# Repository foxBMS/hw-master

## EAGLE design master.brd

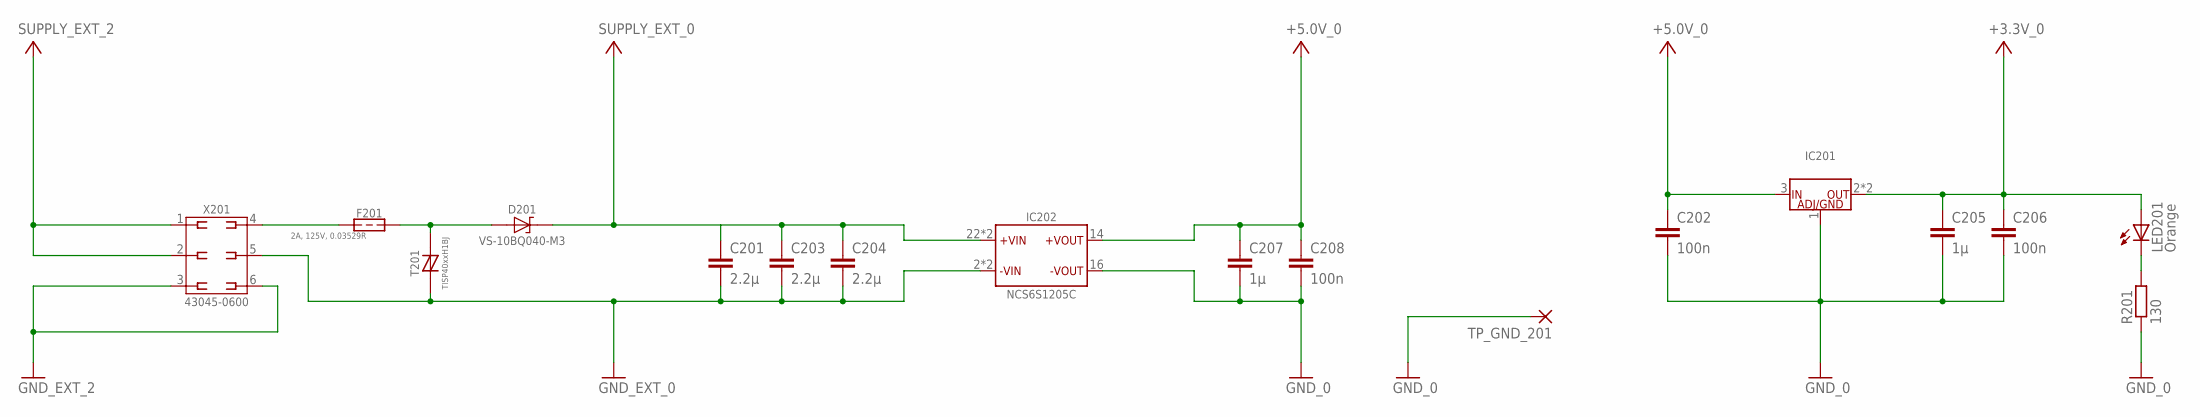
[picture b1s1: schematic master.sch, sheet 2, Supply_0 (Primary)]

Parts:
C201, C203, C204: 2.2µ; C0805
C202, C206, C208: 100n; C0603
C205, C207: 1µ; C0603
D201: VS-10BQ040-M3; D_SMD_SMB_(DO-214AA)_R_VISHAY_REV01
F201: 0,500A_LITTELFUSE_4482A; 448_SERIES_LITTELFUSE
IC201: LM1085IS-5.0/NOPB; IC_SMD_TO-263-3_(KTT0003B)_R_TI_REV01
IC202: MURATA_NCS6S1205C; IC_TH_32,00MMX20,00MMX10,00MM_(7-PIN)_R_MURATA_REV01
LED201: Orange; CHIP-LED0603
R201: 130; R0603
T201: TISP40XXH1BJ; TVS_THYRISTOR
TP_GND_201: 1,6/0,8
X201: 43045-0600_MOLEX_6PIN; X_TH_MOLEX_43045-0600_R_REV01

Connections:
+3.3V_0: C205.1, C206.1, IC201.2 (OUT), IC201.4 (OUT), LED201.A; also elsewhere on the board
+5.0V_0: C202.1, C207.1, C208.1, IC201.3 (IN), IC202.14 (+VOUT); also elsewhere on the board
GND_0: C202.2, C205.2, C206.2, C207.2, C208.2, IC201.1 (ADJ/GND), IC202.16 (-VOUT), R201.1, TP_GND_201.1; also elsewhere on the board
GND_EXT_0: C201.2, C203.2, C204.2, IC202.2 (-VIN), IC202.3 (-VIN), T201.C (T), X201.5; also elsewhere on the board
GND_EXT_2: X201.3, X201.6; also elsewhere on the board
unnamed: LED201.C, R201.2
unnamed: D201.A, F201.P$2, T201.A (R)
unnamed: F201.P$1, X201.4
SUPPLY_EXT_0: C201.1, C203.1, C204.1, D201.C, IC202.22 (+VIN), IC202.23 (+VIN); also elsewhere on the board
SUPPLY_EXT_2: X201.1, X201.2; also elsewhere on the board

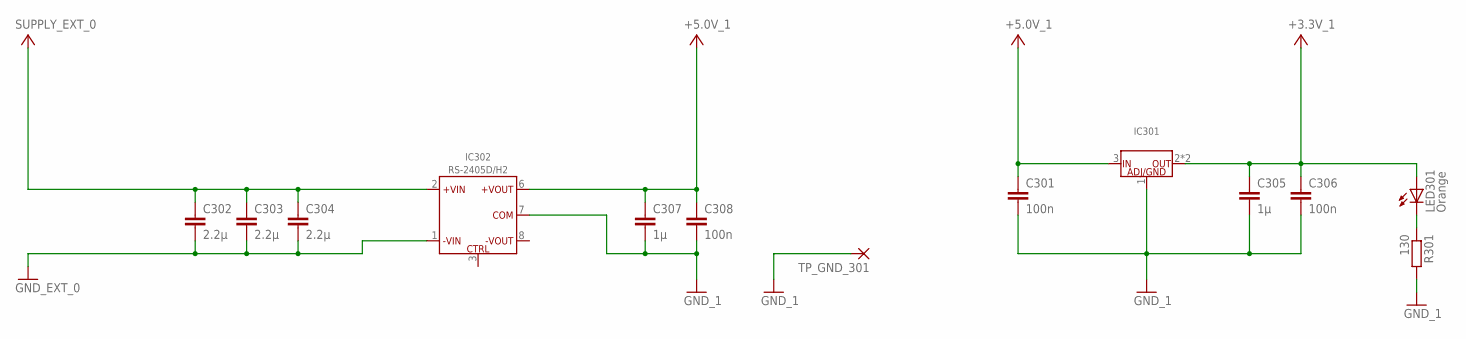
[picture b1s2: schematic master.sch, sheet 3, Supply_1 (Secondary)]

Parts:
C301, C306, C308: 100n; C0603
C302, C303, C304: 2.2µ; C0805
C305, C307: 1µ; C0603
IC301: LM1085IS-5.0/NOPB; IC_SMD_TO-263-3_(KTT0003B)_R_TI_REV01
IC302: RS-2405D/H2; IC_TH_SIP8_R_RECOM_REV01
LED301: Orange; CHIP-LED0603
R301: 130; R0603
TP_GND_301: 1,6/0,8

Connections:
+3.3V_1: C305.1, C306.1, IC301.2 (OUT), IC301.4 (OUT), LED301.A; also elsewhere on the board
+5.0V_1: C301.1, C307.1, C308.1, IC301.3 (IN), IC302.6 (+VOUT); also elsewhere on the board
GND_1: C301.2, C305.2, C306.2, C307.2, C308.2, IC301.1 (ADJ/GND), IC302.7 (COM), R301.2, TP_GND_301.1; also elsewhere on the board
GND_EXT_0: C302.2, C303.2, C304.2, IC302.1 (-VIN); also elsewhere on the board
unnamed: LED301.C, R301.1
SUPPLY_EXT_0: C302.1, C303.1, C304.1, IC302.2 (+VIN); also elsewhere on the board

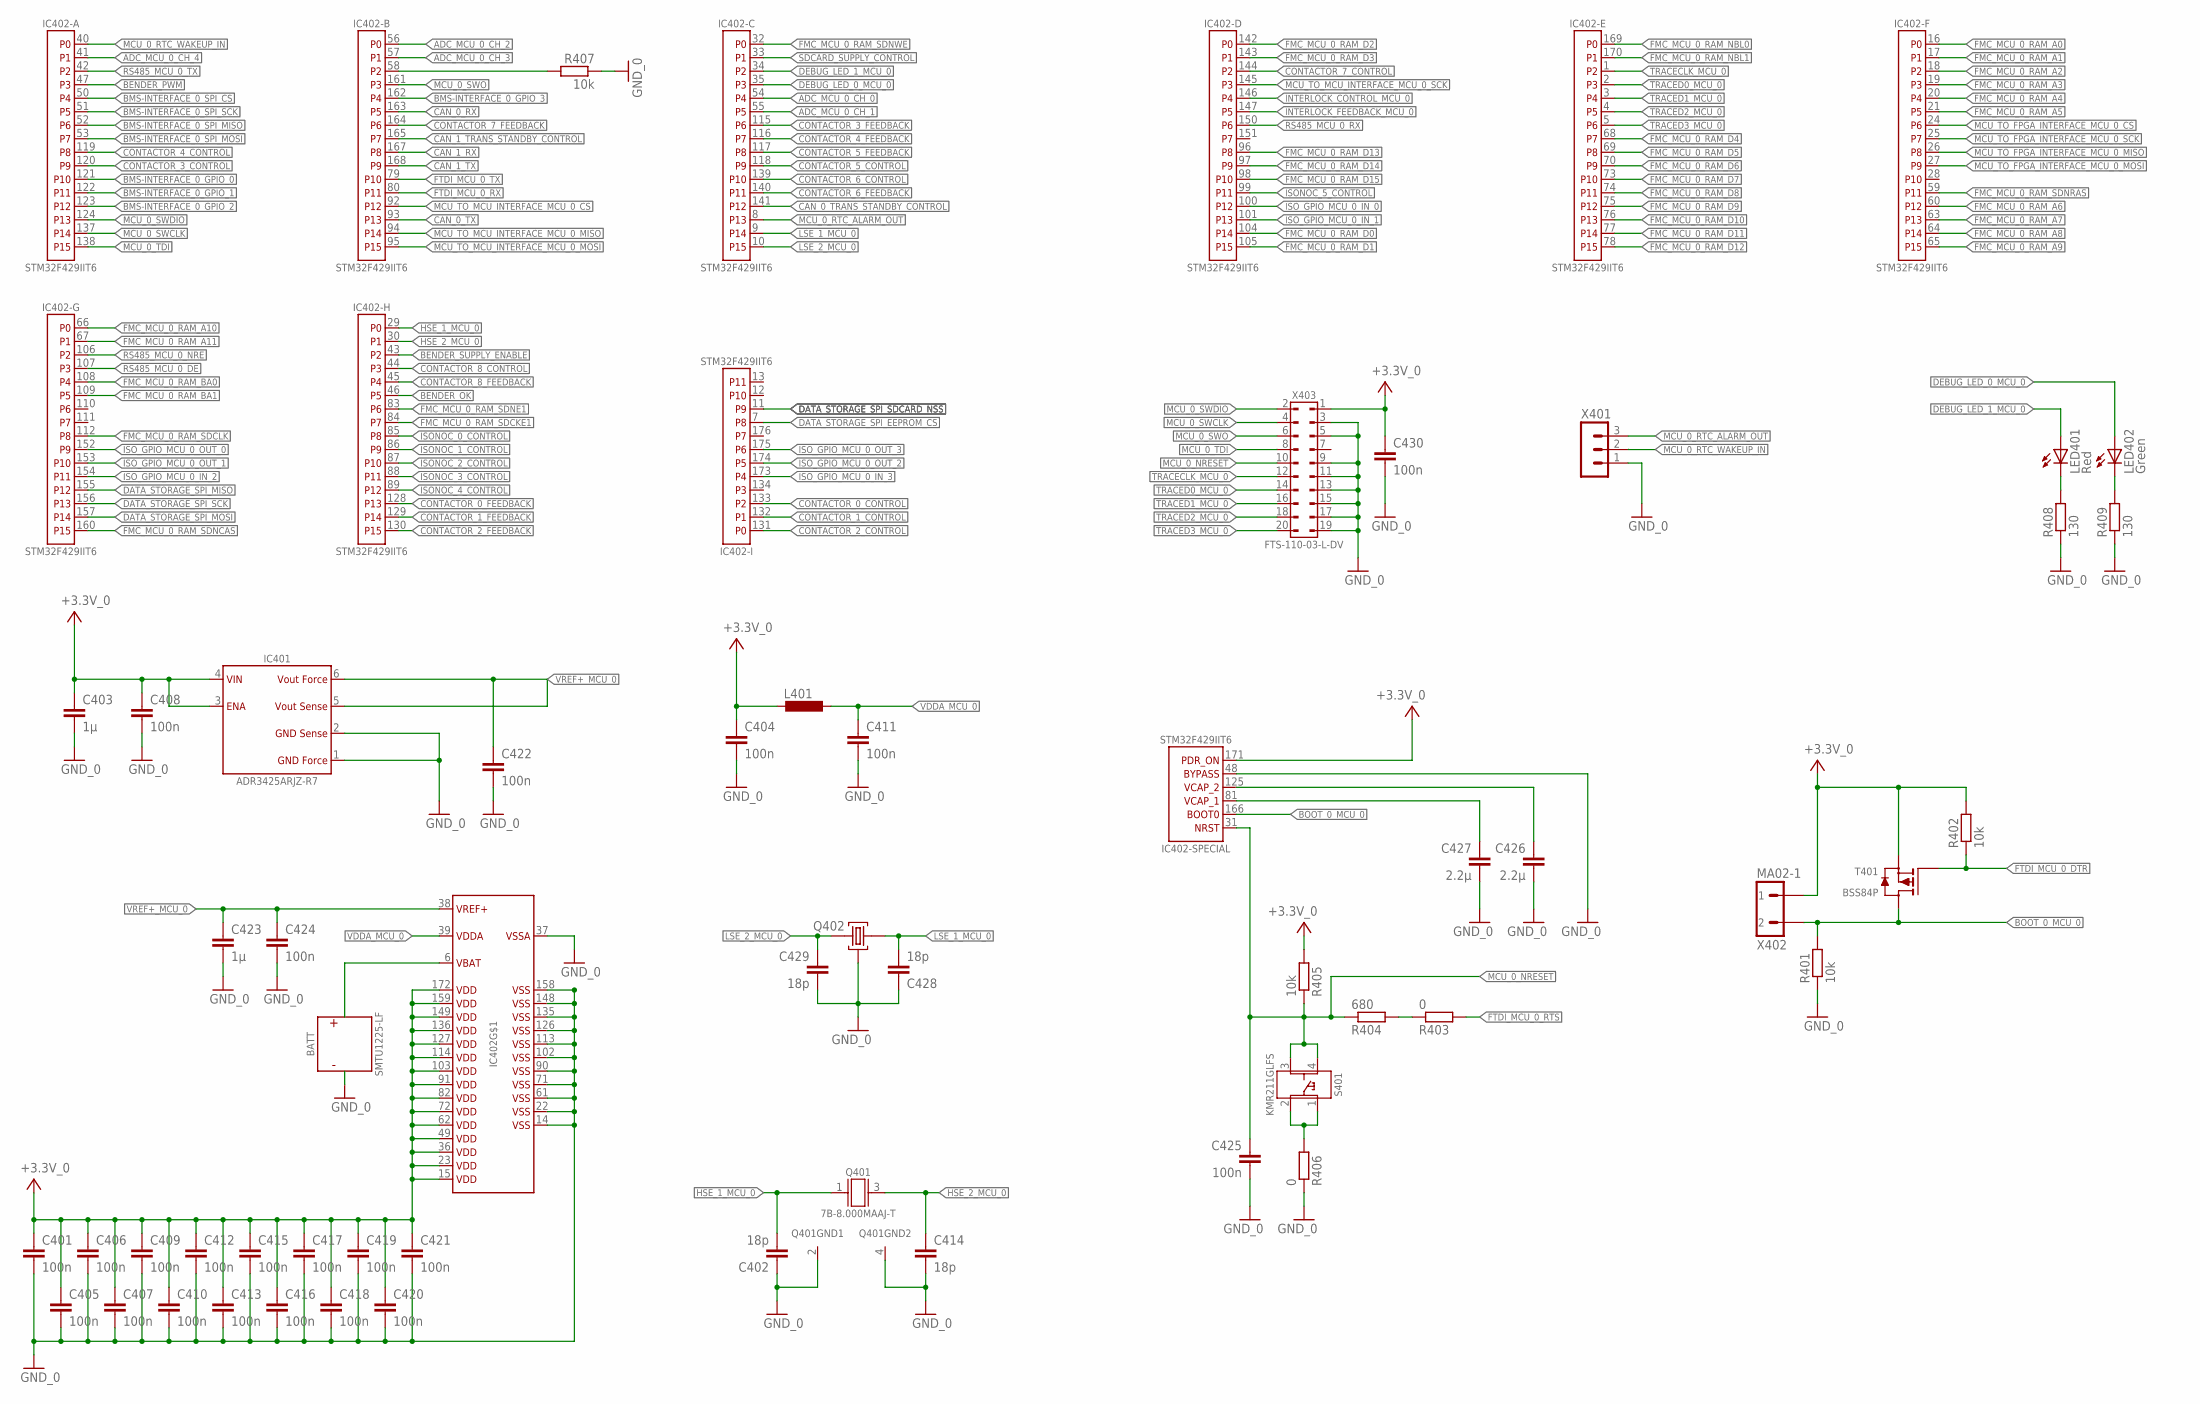
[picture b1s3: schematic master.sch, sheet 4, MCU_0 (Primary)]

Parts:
BATT: SMTU1225-LF; X_SMD_(23,70MM_X_12,70MM_X_5,00MM)_R_RENATA_REV01
C401, C404, C405, C406, C407, C408, C409, C410, C411, C412, C413, C415, C416, C417, C418, C419, C420, C421, C422, C424, C425, C430: 100n; C0603
C402, C414, C428, C429: 18p; C0603
C403, C423: 1µ; C0603
C426, C427: 2.2µ; C0603
IC401: ADR3425ARJZ; IC_SMD_SOT23-6_(MO-178-AB)_R_AD_REV01
IC402: STM32F429IIT6; IC_SMD_LQFP176_R_ST_REV01
L401: L0805; 0805
LED401: Red; CHIP-LED0603
LED402: Green; CHIP-LED0603
Q401: 7B-8.000MAAJ-T; G_SMD_5,00MM_X_3,20MM_0,90MM_(7B)_TXC_REV01
Q402: MS3V; MS3V-T1R
R401, R402, R405, R407: 10k; R0603
R403, R406: 0; R0603
R404: 680; R0603
R408, R409: 130; R0603
S401: KMR211GLFS; S_SMD_4,60MMX2,80MMX1,90MM_R_CK-COMPONENTS_REV01
T401: BSS84P; V_SMD_SOT23_(TO-236AB)_R_INFINEON_REV01
X401: MA03-1
X402: MA02-1
X403: SAMTEC_FTS_20POL_HEADER_VERTIKAL_REV01; X_SMD_FTS_110-03_(20POL)_R_SAMTEC_REV01

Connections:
+3.3V_0: C401.1, C403.1, C404.1, C405.1, C406.1, C407.1, C408.1, C409.1, C410.1, C412.1, C413.1, C415.1, C416.1, C417.1, C418.1, C419.1, C420.1, C421.1, C430.1, IC401.3 (ENABLE), IC401.4 (VIN), IC402.15 (VDD1), IC402.23 (VDD2), IC402.36 (VDD3), IC402.49 (VDD4), IC402.62 (VDD5), IC402.72 (VDD6), IC402.82 (VDD7), IC402.91 (VDD8), IC402.103 (VDD9), IC402.114 (VDD10), IC402.127 (VDD11), IC402.136 (VDD12), IC402.149 (VDD13), IC402.159 (VDD14), IC402.171 (PDR_ON), IC402.172 (VDD15), L401.1, R402.2, R405.2, T401.2 (S), X402.1, X403.1; also elsewhere on the board
ADC_MCU_0_CH_0: IC402.54 (P4); also elsewhere on the board
ADC_MCU_0_CH_1: IC402.55 (P5); also elsewhere on the board
ADC_MCU_0_CH_2: IC402.56 (P0); also elsewhere on the board
ADC_MCU_0_CH_3: IC402.57 (P1); also elsewhere on the board
ADC_MCU_0_CH_4: IC402.41 (P1); also elsewhere on the board
BENDER_OK: IC402.46 (P5); also elsewhere on the board
BENDER_PWM: IC402.47 (P3); also elsewhere on the board
BENDER_SUPPLY_ENABLE: IC402.43 (P2); also elsewhere on the board
BMS-INTERFACE_0_GPIO_0: IC402.121 (P10); also elsewhere on the board
BMS-INTERFACE_0_GPIO_1: IC402.122 (P11); also elsewhere on the board
BMS-INTERFACE_0_GPIO_2: IC402.123 (P12); also elsewhere on the board
BMS-INTERFACE_0_GPIO_3: IC402.162 (P4); also elsewhere on the board
BMS-INTERFACE_0_SPI_CS: IC402.50 (P4); also elsewhere on the board
BMS-INTERFACE_0_SPI_MISO: IC402.52 (P6); also elsewhere on the board
BMS-INTERFACE_0_SPI_MOSI: IC402.53 (P7); also elsewhere on the board
BMS-INTERFACE_0_SPI_SCK: IC402.51 (P5); also elsewhere on the board
BOOT_0_MCU_0: IC402.166 (BOOT0), R401.2, T401.3 (D), X402.2
CAN_0_RX: IC402.163 (P5); also elsewhere on the board
CAN_0_TRANS_STANDBY_CONTROL: IC402.141 (P12); also elsewhere on the board
CAN_0_TX: IC402.93 (P13); also elsewhere on the board
CAN_1_RX: IC402.167 (P8); also elsewhere on the board
CAN_1_TRANS_STANDBY_CONTROL: IC402.165 (P7); also elsewhere on the board
CAN_1_TX: IC402.168 (P9); also elsewhere on the board
CONTACTOR_0_CONTROL: IC402.133 (P2); also elsewhere on the board
CONTACTOR_0_FEEDBACK: IC402.128 (P13); also elsewhere on the board
CONTACTOR_1_CONTROL: IC402.132 (P1); also elsewhere on the board
CONTACTOR_1_FEEDBACK: IC402.129 (P14); also elsewhere on the board
CONTACTOR_2_CONTROL: IC402.131 (P0); also elsewhere on the board
CONTACTOR_2_FEEDBACK: IC402.130 (P15); also elsewhere on the board
CONTACTOR_3_CONTROL: IC402.120 (P9); also elsewhere on the board
CONTACTOR_3_FEEDBACK: IC402.115 (P6); also elsewhere on the board
CONTACTOR_4_CONTROL: IC402.119 (P8); also elsewhere on the board
CONTACTOR_4_FEEDBACK: IC402.116 (P7); also elsewhere on the board
CONTACTOR_5_CONTROL: IC402.118 (P9); also elsewhere on the board
CONTACTOR_5_FEEDBACK: IC402.117 (P8); also elsewhere on the board
CONTACTOR_6_CONTROL: IC402.139 (P10); also elsewhere on the board
CONTACTOR_6_FEEDBACK: IC402.140 (P11); also elsewhere on the board
CONTACTOR_7_CONTROL: IC402.144 (P2); also elsewhere on the board
CONTACTOR_7_FEEDBACK: IC402.164 (P6); also elsewhere on the board
CONTACTOR_8_CONTROL: IC402.44 (P3); also elsewhere on the board
CONTACTOR_8_FEEDBACK: IC402.45 (P4); also elsewhere on the board
DATA_STORAGE_SPI_EEPROM_CS: IC402.7 (P8); also elsewhere on the board
DATA_STORAGE_SPI_MISO: IC402.155 (P12); also elsewhere on the board
DATA_STORAGE_SPI_MOSI: IC402.157 (P14); also elsewhere on the board
DATA_STORAGE_SPI_SCK: IC402.156 (P13); also elsewhere on the board
DATA_STORAGE_SPI_SDCARD_NSS: IC402.11 (P9); also elsewhere on the board
DEBUG_LED_0_MCU_0: IC402.35 (P3), LED402.A
DEBUG_LED_1_MCU_0: IC402.34 (P2), LED401.A
FMC_MCU_0_RAM_A0: IC402.16 (P0); also elsewhere on the board
FMC_MCU_0_RAM_A1: IC402.17 (P1); also elsewhere on the board
FMC_MCU_0_RAM_A2: IC402.18 (P2); also elsewhere on the board
FMC_MCU_0_RAM_A3: IC402.19 (P3); also elsewhere on the board
FMC_MCU_0_RAM_A4: IC402.20 (P4); also elsewhere on the board
FMC_MCU_0_RAM_A5: IC402.21 (P5); also elsewhere on the board
FMC_MCU_0_RAM_A6: IC402.60 (P12); also elsewhere on the board
FMC_MCU_0_RAM_A7: IC402.63 (P13); also elsewhere on the board
FMC_MCU_0_RAM_A8: IC402.64 (P14); also elsewhere on the board
FMC_MCU_0_RAM_A9: IC402.65 (P15); also elsewhere on the board
FMC_MCU_0_RAM_A10: IC402.66 (P0); also elsewhere on the board
FMC_MCU_0_RAM_A11: IC402.67 (P1); also elsewhere on the board
FMC_MCU_0_RAM_BA0: IC402.108 (P4); also elsewhere on the board
FMC_MCU_0_RAM_BA1: IC402.109 (P5); also elsewhere on the board
FMC_MCU_0_RAM_D0: IC402.104 (P14); also elsewhere on the board
FMC_MCU_0_RAM_D1: IC402.105 (P15); also elsewhere on the board
FMC_MCU_0_RAM_D2: IC402.142 (P0); also elsewhere on the board
FMC_MCU_0_RAM_D3: IC402.143 (P1); also elsewhere on the board
FMC_MCU_0_RAM_D4: IC402.68 (P7); also elsewhere on the board
FMC_MCU_0_RAM_D5: IC402.69 (P8); also elsewhere on the board
FMC_MCU_0_RAM_D6: IC402.70 (P9); also elsewhere on the board
FMC_MCU_0_RAM_D7: IC402.73 (P10); also elsewhere on the board
FMC_MCU_0_RAM_D8: IC402.74 (P11); also elsewhere on the board
FMC_MCU_0_RAM_D9: IC402.75 (P12); also elsewhere on the board
FMC_MCU_0_RAM_D10: IC402.76 (P13); also elsewhere on the board
FMC_MCU_0_RAM_D11: IC402.77 (P14); also elsewhere on the board
FMC_MCU_0_RAM_D12: IC402.78 (P15); also elsewhere on the board
FMC_MCU_0_RAM_D13: IC402.96 (P8); also elsewhere on the board
FMC_MCU_0_RAM_D14: IC402.97 (P9); also elsewhere on the board
FMC_MCU_0_RAM_D15: IC402.98 (P10); also elsewhere on the board
FMC_MCU_0_RAM_NBL0: IC402.169 (P0); also elsewhere on the board
FMC_MCU_0_RAM_NBL1: IC402.170 (P1); also elsewhere on the board
FMC_MCU_0_RAM_SDCKE1: IC402.84 (P7); also elsewhere on the board
FMC_MCU_0_RAM_SDCLK: IC402.112 (P8); also elsewhere on the board
FMC_MCU_0_RAM_SDNCAS: IC402.160 (P15); also elsewhere on the board
FMC_MCU_0_RAM_SDNE1: IC402.83 (P6); also elsewhere on the board
FMC_MCU_0_RAM_SDNRAS: IC402.59 (P11); also elsewhere on the board
FMC_MCU_0_RAM_SDNWE: IC402.32 (P0); also elsewhere on the board
FTDI_MCU_0_DTR: R402.1, T401.1 (G); also elsewhere on the board
FTDI_MCU_0_RTS: R403.2; also elsewhere on the board
FTDI_MCU_0_RX: IC402.80 (P11); also elsewhere on the board
FTDI_MCU_0_TX: IC402.79 (P10); also elsewhere on the board
GND_0: BATT.-, C401.2, C402.1, C403.2, C404.2, C405.2, C406.2, C407.2, C408.2, C409.2, C410.2, C411.2, C412.2, C413.2, C414.2, C415.2, C416.2, C417.2, C418.2, C419.2, C420.2, C421.2, C422.2, C423.2, C424.2, C425.2, C426.2, C427.2, C428.1, C429.2, C430.2, IC401.1 (GND_FORCE), IC401.2 (GND_SENSE), IC402.14 (VSS1), IC402.22 (VSS2), IC402.37 (VSSA), IC402.48 (BYPASS_REG), IC402.61 (VSS3), IC402.71 (VSS4), IC402.90 (VSS5), IC402.102 (VSS6), IC402.113 (VSS7), IC402.126 (VSS8), IC402.135 (VSS9), IC402.148 (VSS10), IC402.158 (VSS11), Q401.2 (GND), Q401.4 (GND), Q402.P$3 (2), R401.1, R406.1, R407.1, R408.1, R409.1, X401.1, X403.3, X403.5, X403.9, X403.11, X403.13, X403.15, X403.17, X403.19; also elsewhere on the board
HSE_1_MCU_0: C402.2, IC402.29 (P0), Q401.1 (A)
HSE_2_MCU_0: C414.1, IC402.30 (P1), Q401.3 (B)
INTERLOCK_CONTROL_MCU_0: IC402.146 (P4); also elsewhere on the board
INTERLOCK_FEEDBACK_MCU_0: IC402.147 (P5); also elsewhere on the board
ISONOC_0_CONTROL: IC402.85 (P8); also elsewhere on the board
ISONOC_1_CONTROL: IC402.86 (P9); also elsewhere on the board
ISONOC_2_CONTROL: IC402.87 (P10); also elsewhere on the board
ISONOC_3_CONTROL: IC402.88 (P11); also elsewhere on the board
ISONOC_4_CONTROL: IC402.89 (P12); also elsewhere on the board
ISONOC_5_CONTROL: IC402.99 (P11); also elsewhere on the board
ISO_GPIO_MCU_0_IN_0: IC402.100 (P12); also elsewhere on the board
ISO_GPIO_MCU_0_IN_1: IC402.101 (P13); also elsewhere on the board
ISO_GPIO_MCU_0_IN_2: IC402.154 (P11); also elsewhere on the board
ISO_GPIO_MCU_0_IN_3: IC402.173 (P4); also elsewhere on the board
ISO_GPIO_MCU_0_OUT_0: IC402.152 (P9); also elsewhere on the board
ISO_GPIO_MCU_0_OUT_1: IC402.153 (P10); also elsewhere on the board
ISO_GPIO_MCU_0_OUT_2: IC402.174 (P5); also elsewhere on the board
ISO_GPIO_MCU_0_OUT_3: IC402.175 (P6); also elsewhere on the board
LSE_1_MCU_0: C428.2, IC402.9 (P14), Q402.1
LSE_2_MCU_0: C429.1, IC402.10 (P15), Q402.2 (3)
MCU_0_NRESET: C425.1, IC402.31 (NRST), R404.1, R405.1, S401.3, S401.4, X403.10
MCU_0_RTC_ALARM_OUT: IC402.8 (P13), X401.3
MCU_0_RTC_WAKEUP_IN: IC402.40 (P0), X401.2
MCU_0_SWCLK: IC402.137 (P14), X403.4
MCU_0_SWDIO: IC402.124 (P13), X403.2
MCU_0_SWO: IC402.161 (P3), X403.6
MCU_0_TDI: IC402.138 (P15), X403.8
MCU_TO_FPGA_INTERFACE_MCU_0_CS: IC402.24 (P6); also elsewhere on the board
MCU_TO_FPGA_INTERFACE_MCU_0_MISO: IC402.26 (P8); also elsewhere on the board
MCU_TO_FPGA_INTERFACE_MCU_0_MOSI: IC402.27 (P9); also elsewhere on the board
MCU_TO_FPGA_INTERFACE_MCU_0_SCK: IC402.25 (P7); also elsewhere on the board
MCU_TO_MCU_INTERFACE_MCU_0_CS: IC402.92 (P12); also elsewhere on the board
MCU_TO_MCU_INTERFACE_MCU_0_MISO: IC402.94 (P14); also elsewhere on the board
MCU_TO_MCU_INTERFACE_MCU_0_MOSI: IC402.95 (P15); also elsewhere on the board
MCU_TO_MCU_INTERFACE_MCU_0_SCK: IC402.145 (P3); also elsewhere on the board
unnamed: C426.1, IC402.125 (VCAP_2)
unnamed: R406.2, S401.1, S401.2
unnamed: LED401.C, R408.2
unnamed: LED402.C, R409.2
unnamed: C427.1, IC402.81 (VCAP_1)
unnamed: IC402.58 (P2), R407.2
unnamed: R403.1, R404.2
unnamed: BATT.+, IC402.6 (VBAT)
RS485_MCU_0_DE: IC402.107 (P3); also elsewhere on the board
RS485_MCU_0_NRE: IC402.106 (P2); also elsewhere on the board
RS485_MCU_0_RX: IC402.150 (P6); also elsewhere on the board
RS485_MCU_0_TX: IC402.42 (P2); also elsewhere on the board
SDCARD_SUPPLY_CONTROL: IC402.33 (P1); also elsewhere on the board
TRACECLK_MCU_0: IC402.1 (P2), X403.12
TRACED0_MCU_0: IC402.2 (P3), X403.14
TRACED1_MCU_0: IC402.3 (P4), X403.16
TRACED2_MCU_0: IC402.4 (P5), X403.18
TRACED3_MCU_0: IC402.5 (P6), X403.20
VDDA_MCU_0: C411.1, IC402.39 (VDDA), L401.2
VREF+_MCU_0: C422.1, C423.1, C424.1, IC401.5 (VOUT_SENSE), IC401.6 (VOUT_FORCE), IC402.38 (VREF+)

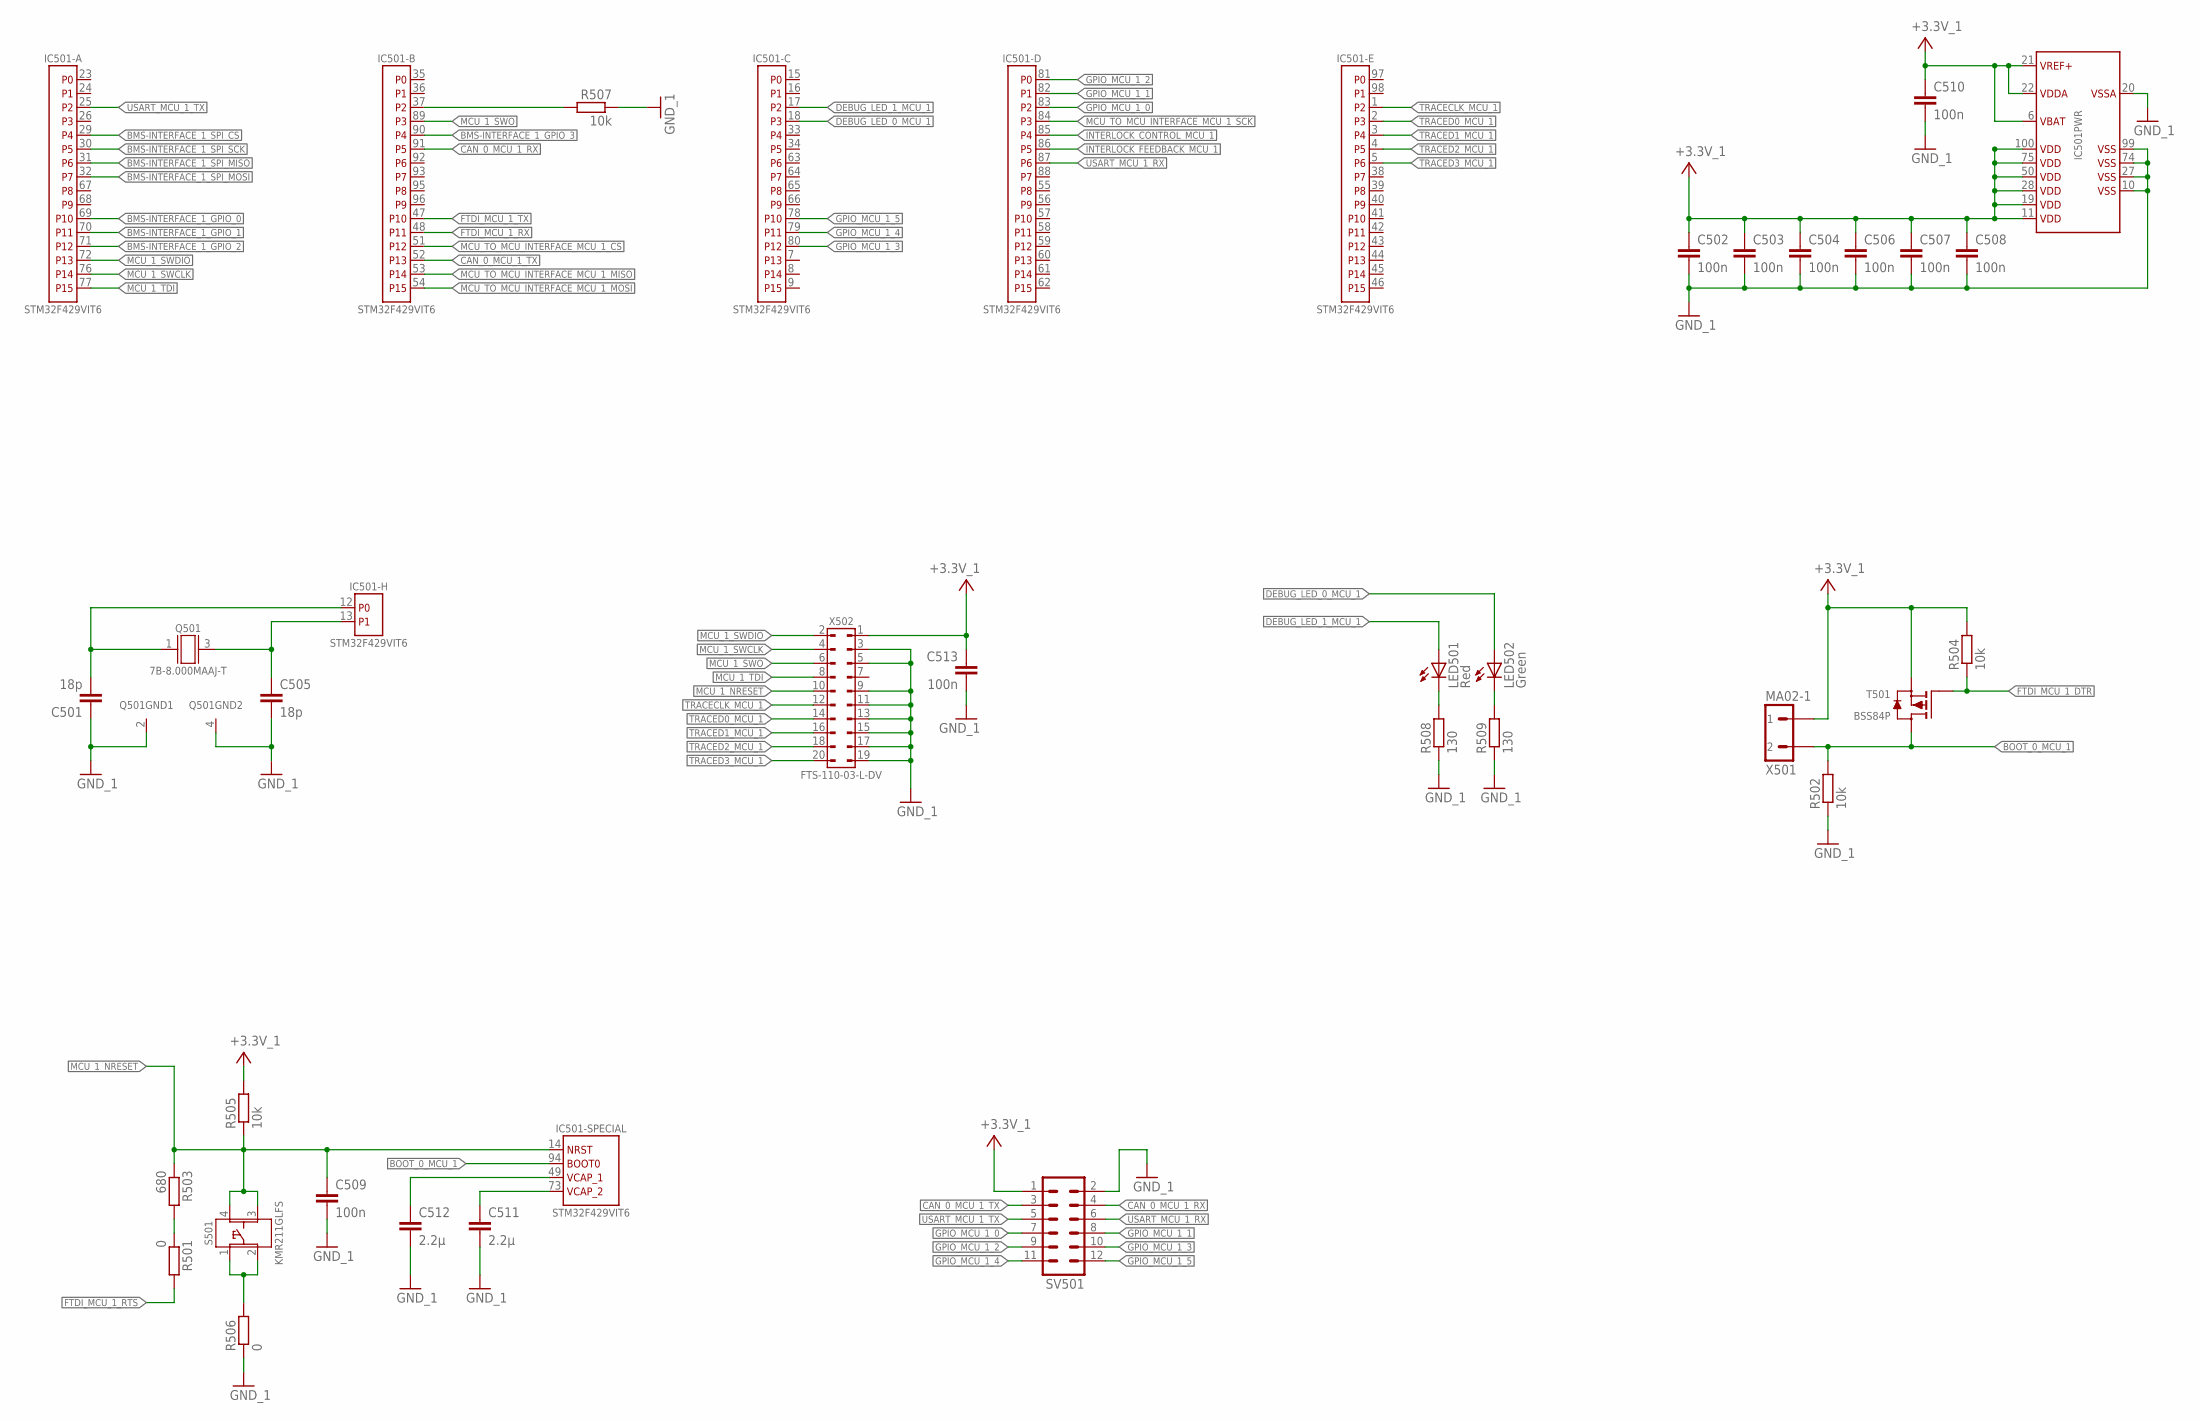
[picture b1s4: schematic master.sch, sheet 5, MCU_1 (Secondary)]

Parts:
C501, C505: 18p; C0603
C502, C503, C504, C506, C507, C508, C509, C510, C513: 100n; C0603
C511, C512: 2.2µ; C0603
IC501: STM32F429VIT6; IC_SMD_LQFP100_R_ST_REV01
LED501: Red; CHIP-LED0603
LED502: Green; CHIP-LED0603
Q501: 7B-8.000MAAJ-T; G_SMD_5,00MM_X_3,20MM_0,90MM_(7B)_TXC_REV01
R501, R506: 0; R0603
R502, R504, R505, R507: 10k; R0603
R503: 680; R0603
R508, R509: 130; R0603
S501: KMR211GLFS; S_SMD_4,60MMX2,80MMX1,90MM_R_CK-COMPONENTS_REV01
SV501: MA06-2
T501: BSS84P; V_SMD_SOT23_(TO-236AB)_R_INFINEON_REV01
X501: MA02-1
X502: SAMTEC_FTS_20POL_HEADER_VERTIKAL_REV01; X_SMD_FTS_110-03_(20POL)_R_SAMTEC_REV01

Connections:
+3.3V_1: C502.1, C503.1, C504.1, C506.1, C507.1, C508.1, C510.1, C513.1, IC501.6 (VBAT), IC501.11 (VDD1), IC501.19 (VDD2), IC501.21 (VREF+), IC501.22 (VDDA), IC501.28 (VDD3), IC501.50 (VDD4), IC501.75 (VDD5), IC501.100 (VDD6), R504.2, R505.2, SV501.1, T501.2 (S), X501.1, X502.1; also elsewhere on the board
BMS-INTERFACE_1_GPIO_0: IC501.69 (P10); also elsewhere on the board
BMS-INTERFACE_1_GPIO_1: IC501.70 (P11); also elsewhere on the board
BMS-INTERFACE_1_GPIO_2: IC501.71 (P12); also elsewhere on the board
BMS-INTERFACE_1_GPIO_3: IC501.90 (P4); also elsewhere on the board
BMS-INTERFACE_1_SPI_CS: IC501.29 (P4); also elsewhere on the board
BMS-INTERFACE_1_SPI_MISO: IC501.31 (P6); also elsewhere on the board
BMS-INTERFACE_1_SPI_MOSI: IC501.32 (P7); also elsewhere on the board
BMS-INTERFACE_1_SPI_SCK: IC501.30 (P5); also elsewhere on the board
BOOT_0_MCU_1: IC501.94 (BOOT0), R502.2, T501.3 (D), X501.2
CAN_0_MCU_1_RX: IC501.91 (P5), SV501.4
CAN_0_MCU_1_TX: IC501.52 (P13), SV501.3
DEBUG_LED_0_MCU_1: IC501.18 (P3), LED502.A
DEBUG_LED_1_MCU_1: IC501.17 (P2), LED501.A
FTDI_MCU_1_DTR: R504.1, T501.1 (G); also elsewhere on the board
FTDI_MCU_1_RTS: R501.2; also elsewhere on the board
FTDI_MCU_1_RX: IC501.48 (P11); also elsewhere on the board
FTDI_MCU_1_TX: IC501.47 (P10); also elsewhere on the board
GND_1: C501.1, C502.2, C503.2, C504.2, C505.2, C506.2, C507.2, C508.2, C509.2, C510.2, C511.2, C512.2, C513.2, IC501.10 (VSS1), IC501.20 (VSSA), IC501.27 (VSS2), IC501.74 (VSS3), IC501.99 (VSS4), Q501.2 (GND), Q501.4 (GND), R502.1, R506.1, R507.1, R508.1, R509.1, SV501.2, X502.3, X502.5, X502.9, X502.11, X502.13, X502.15, X502.17, X502.19; also elsewhere on the board
GPIO_MCU_1_0: IC501.83 (P2), SV501.7
GPIO_MCU_1_1: IC501.82 (P1), SV501.8
GPIO_MCU_1_2: IC501.81 (P0), SV501.9
GPIO_MCU_1_3: IC501.80 (P12), SV501.10
GPIO_MCU_1_4: IC501.79 (P11), SV501.11
GPIO_MCU_1_5: IC501.78 (P10), SV501.12
INTERLOCK_CONTROL_MCU_1: IC501.85 (P4); also elsewhere on the board
INTERLOCK_FEEDBACK_MCU_1: IC501.86 (P5); also elsewhere on the board
MCU_1_NRESET: C509.1, IC501.14 (NRST), R503.1, R505.1, S501.3, S501.4, X502.10
MCU_1_SWCLK: IC501.76 (P14), X502.4
MCU_1_SWDIO: IC501.72 (P13), X502.2
MCU_1_SWO: IC501.89 (P3), X502.6
MCU_1_TDI: IC501.77 (P15), X502.8
MCU_TO_MCU_INTERFACE_MCU_1_CS: IC501.51 (P12); also elsewhere on the board
MCU_TO_MCU_INTERFACE_MCU_1_MISO: IC501.53 (P14); also elsewhere on the board
MCU_TO_MCU_INTERFACE_MCU_1_MOSI: IC501.54 (P15); also elsewhere on the board
MCU_TO_MCU_INTERFACE_MCU_1_SCK: IC501.84 (P3); also elsewhere on the board
unnamed: C501.2, IC501.12 (P0), Q501.1 (A)
unnamed: C505.1, IC501.13 (P1), Q501.3 (B)
unnamed: R506.2, S501.1, S501.2
unnamed: LED502.C, R509.2
unnamed: LED501.C, R508.2
unnamed: C511.1, IC501.73 (VCAP_2)
unnamed: C512.1, IC501.49 (VCAP_1)
unnamed: IC501.37 (P2), R507.2
unnamed: R501.1, R503.2
TRACECLK_MCU_1: IC501.1 (P2), X502.12
TRACED0_MCU_1: IC501.2 (P3), X502.14
TRACED1_MCU_1: IC501.3 (P4), X502.16
TRACED2_MCU_1: IC501.4 (P5), X502.18
TRACED3_MCU_1: IC501.5 (P6), X502.20
USART_MCU_1_RX: IC501.87 (P6), SV501.6
USART_MCU_1_TX: IC501.25 (P2), SV501.5

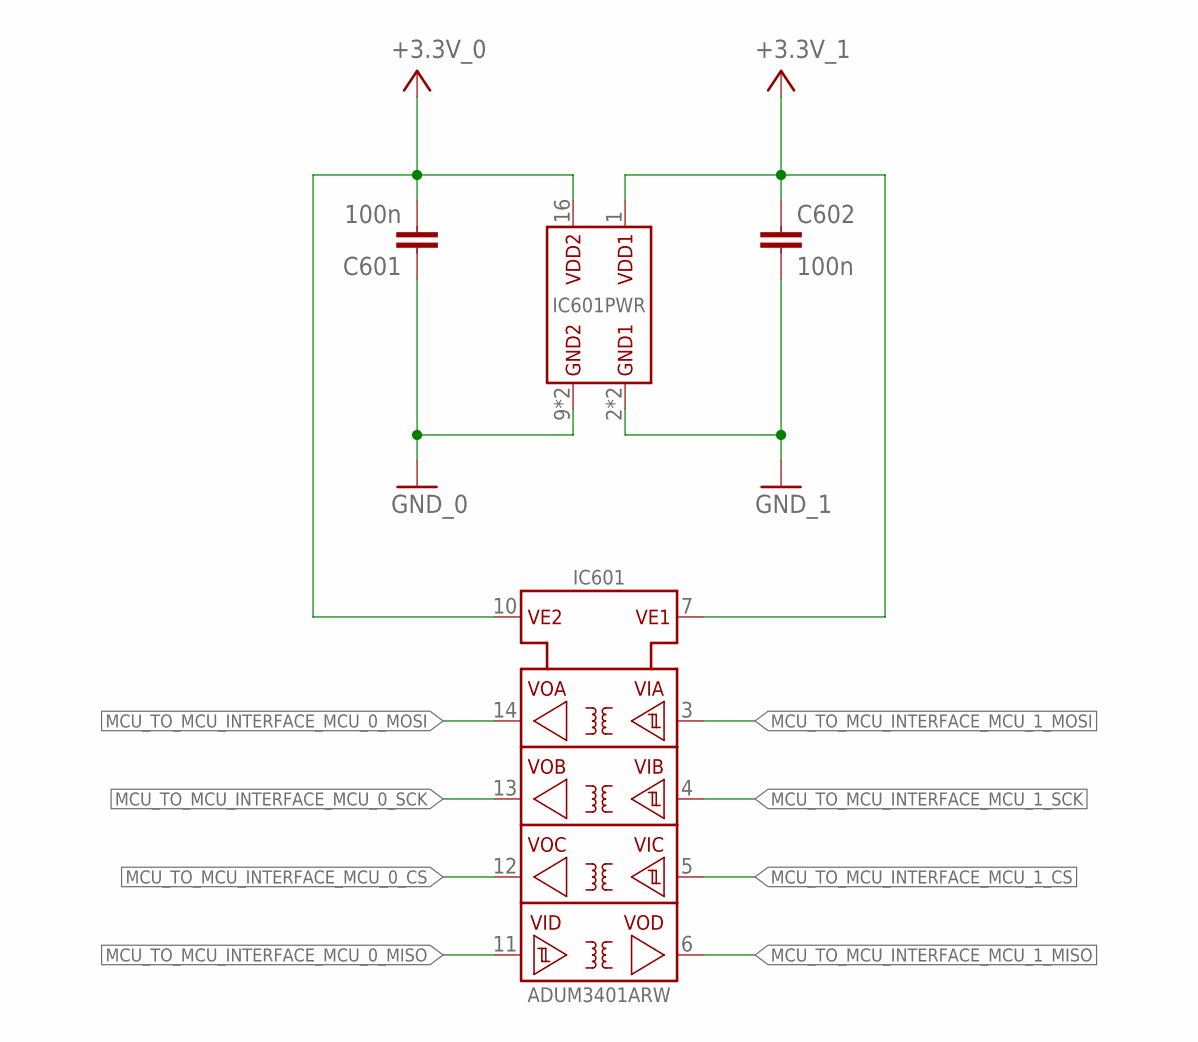
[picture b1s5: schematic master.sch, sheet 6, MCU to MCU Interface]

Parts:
C601, C602: 100n; C0603
IC601: ADUM3401ARW; IC_SMD_SOIC-16_(JEDEC_MS-013-AA)_R_ANALOG_REV01

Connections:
+3.3V_0: C601.2, IC601.10 (VE2), IC601.16 (VDD2); also elsewhere on the board
+3.3V_1: C602.1, IC601.1 (VDD1), IC601.7 (VE1); also elsewhere on the board
GND_0: C601.1, IC601.9 (GND2), IC601.15 (GND2); also elsewhere on the board
GND_1: C602.2, IC601.2 (GND1), IC601.8 (GND1); also elsewhere on the board
MCU_TO_MCU_INTERFACE_MCU_0_CS: IC601.12 (VOC); also elsewhere on the board
MCU_TO_MCU_INTERFACE_MCU_0_MISO: IC601.11 (VID); also elsewhere on the board
MCU_TO_MCU_INTERFACE_MCU_0_MOSI: IC601.14 (VOA); also elsewhere on the board
MCU_TO_MCU_INTERFACE_MCU_0_SCK: IC601.13 (VOB); also elsewhere on the board
MCU_TO_MCU_INTERFACE_MCU_1_CS: IC601.5 (VIC); also elsewhere on the board
MCU_TO_MCU_INTERFACE_MCU_1_MISO: IC601.6 (VOD); also elsewhere on the board
MCU_TO_MCU_INTERFACE_MCU_1_MOSI: IC601.3 (VIA); also elsewhere on the board
MCU_TO_MCU_INTERFACE_MCU_1_SCK: IC601.4 (VIB); also elsewhere on the board

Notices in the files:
master.brd:
Creative Commons
Attribution 4.0
parts and their libraries:
foxBMS_BMS-Master: LICENSE: Creative Commons Attribution 4.0
